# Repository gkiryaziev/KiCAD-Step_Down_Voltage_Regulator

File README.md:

## KiCAD-Step_Down_Voltage_Regulator

[KiCAD](http://kicad-pcb.org/) ([LM2574M-5.0](http://www.ti.com/lit/ds/symlink/lm2574.pdf)) Step-Down Voltage Regulator

### Info
```
This voltage regulator was designed for LM2574M-5.0 and for other pin-to-pin compatible.
This is an early version of the board and is distributed as is.
The missing 3D models you can find on open resources on the Internet.
```

#### License
```
CC BY 4.0
```

### Screenshot

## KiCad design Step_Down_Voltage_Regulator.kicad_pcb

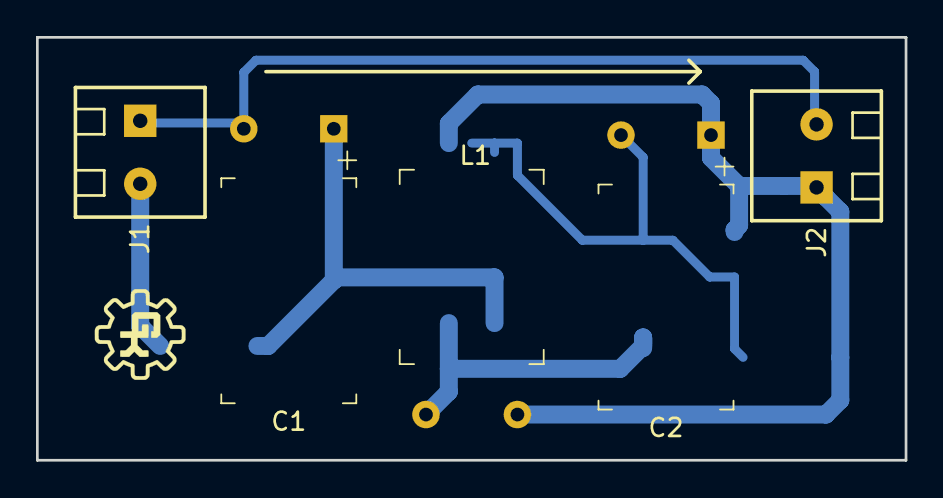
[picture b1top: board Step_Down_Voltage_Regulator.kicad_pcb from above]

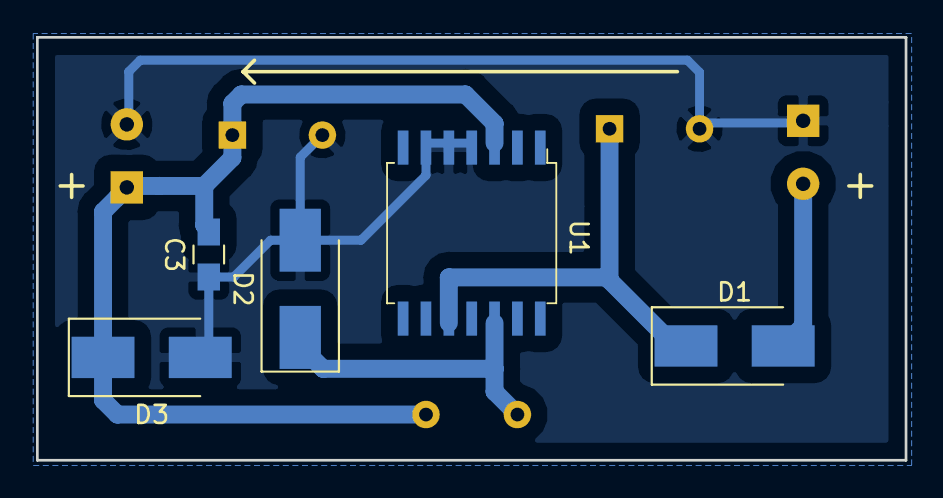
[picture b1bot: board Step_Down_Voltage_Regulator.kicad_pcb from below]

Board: 2 copper layers, 48.3 x 23.5 mm, 10 parts (5 on the bottom side), 5 nets.

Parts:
C1: 47uF 50V; CP_Radial_H12.0mm_D7.0mm_P5.00mm_Horizontal
C2: 100uF 16V; CP_Radial_H12.0mm_D7.0mm_P5.00mm_Horizontal
C3: 100nF; C_0805_HandSoldering
D1: S1G; D_SMB_Handsoldering
D2: B14; D_SMB_Handsoldering
D3: 6V2; D_SMB_Handsoldering
J1: DC In; TerminalBlock_02_P3.50mm
J2: 0.5A Load; TerminalBlock_02_P3.50mm
L1: 220uH; L_Rect_L10.5mm_W7.5mm_P5.00mm_Horizontal
U1: LM2574M-5.0; SOIC-14W_7.5x9.0mm_P1.27mm

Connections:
GND: C1.2, C2.2, C3.2, D2.2, D3.2, J1.1, J2.2, U1.4, U1.5, U1.6
unnamed: C1.1, D1.1, U1.10
unnamed: C2.1, C3.1, D3.1, J2.1, L1.1, U1.3
unnamed: D1.2, J1.2
unnamed: D2.1, L1.2, U1.12
